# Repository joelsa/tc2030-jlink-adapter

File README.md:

# tc2030-jlink-adapter

Adapter to adapt TC2030 to a JLINK Interface.

Works for both TC2030 and TC2030-NL. Contains an Alternative Layout with UART RX and TX on Pins 3 and 6.

<hr>

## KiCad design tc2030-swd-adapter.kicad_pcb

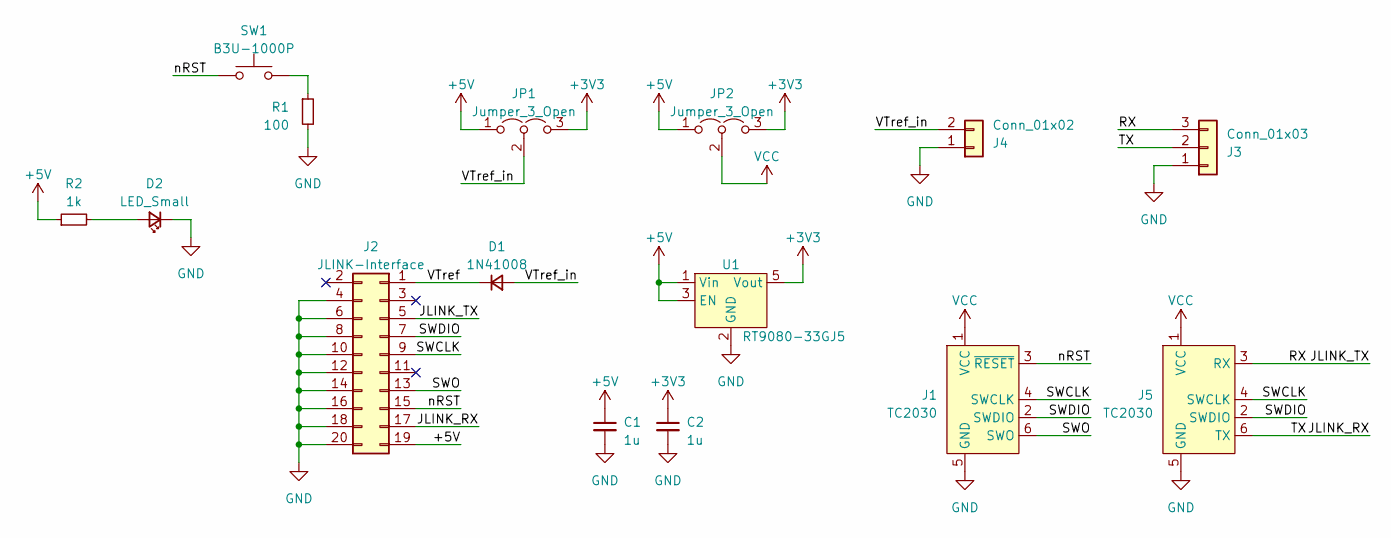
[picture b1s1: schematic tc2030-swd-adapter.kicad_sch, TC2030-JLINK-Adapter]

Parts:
C1, C2: 1u; C_0603_1608Metric
D1: 1N41008; D_SOD-123
D2: LED_Small; LED_0603_1608Metric
J1, J5: TC2030; IDC-Header_2x03_P2.54mm_Vertical
J2: JLINK-Interface; PinSocket_2x10_P2.54mm_Horizontal
J3: Conn_01x03; PinHeader_1x03_P2.54mm_Vertical
J4: Conn_01x02; PinHeader_1x02_P2.54mm_Vertical
JP1, JP2: Jumper_3_Open; PinHeader_1x03_P2.54mm_Vertical
R1: 100; R_0603_1608Metric
R2: 1k; R_0603_1608Metric
SW1: B3U-1000P; SW_SPST_B3U-1000P
U1: RT9080-33GJ5; TSOT-23-5

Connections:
+3V3: C2.1, JP1.3 (B), JP2.3 (B), U1.5 (Vout)
+5V: C1.1, J2.19, JP1.1 (A), JP2.1 (A), R2.1, U1.1 (Vin), U1.3 (EN)
/JLINK_RX: J2.17, J3.2, J5.6 (TX)
/JLINK_TX: J2.5, J3.3, J5.3 (RX)
/SWCLK: J1.4 (SWCLK), J2.9, J5.4 (SWCLK)
/SWDIO: J1.2 (SWDIO), J2.7, J5.2 (SWDIO)
/SWO: J1.6 (SWO), J2.13
/VTref: D1.1 (K), J2.1
/VTref_in: D1.2 (A), J4.2, JP1.2 (C)
/nRST: J1.3 (~RESET), J2.15, SW1.1
GND: C1.2, C2.2, D2.1 (K), J1.5 (GND), J2.4, J2.6, J2.8, J2.10, J2.12, J2.14, J2.16, J2.18, J2.20, J3.1, J4.1, J5.5 (GND), R1.2, U1.2 (GND)
unnamed: D2.2 (A), R2.2
unnamed: R1.1, SW1.2
VCC: J1.1 (VCC), J5.1 (VCC), JP2.2 (C)

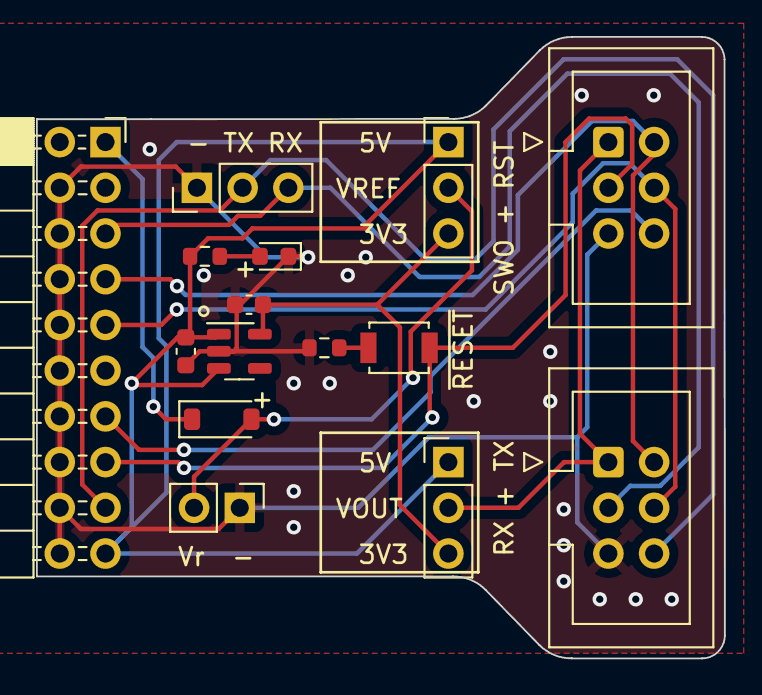
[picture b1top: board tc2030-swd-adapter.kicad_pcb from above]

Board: 2 copper layers, 38.2 x 34.5 mm, 15 parts (0 on the bottom side), 14 nets.

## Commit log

2023-03-23 Initial commmit
2023-03-25 Finish pcb
2023-03-25 Cleanup
2023-03-27 Add UART to JLINK
